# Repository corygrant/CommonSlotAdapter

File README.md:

## CommonSlotAdapter

Adapt HP server power supplies to common high power connectors rather than typical multiple PCI-E connectors.

- Card edge connector: 
    - Amphenol FCI 10053363-200LF [Digikey](https://www.digikey.com/en/products/detail/amphenol-cs-fci/10053363-200LF/1493359?s=N4IgTCBcDaIIwAYEFYDMqBsqC0YkBkAxEAXQF8g)
- Banana jacks: 
    - Cinch 105-0752-001 [Digikey-Red](https://www.digikey.com/en/products/detail/cinch-connectivity-solutions-johnson/105-0752-001/5887) / [Digikey-Black](https://www.digikey.com/en/products/detail/cinch-connectivity-solutions-johnson/105-0753-001/5888) 
- Switch: 
    - Nidec ATE1D-2M3-10-Z [Digikey](https://www.digikey.com/en/products/detail/nidec-components-corporation/ate1d-2m3-10-z/1792018)

Note: I had issues with the typical resistor across 33 and 36. That approach did not work for me. V2 fixes the issues that I had.

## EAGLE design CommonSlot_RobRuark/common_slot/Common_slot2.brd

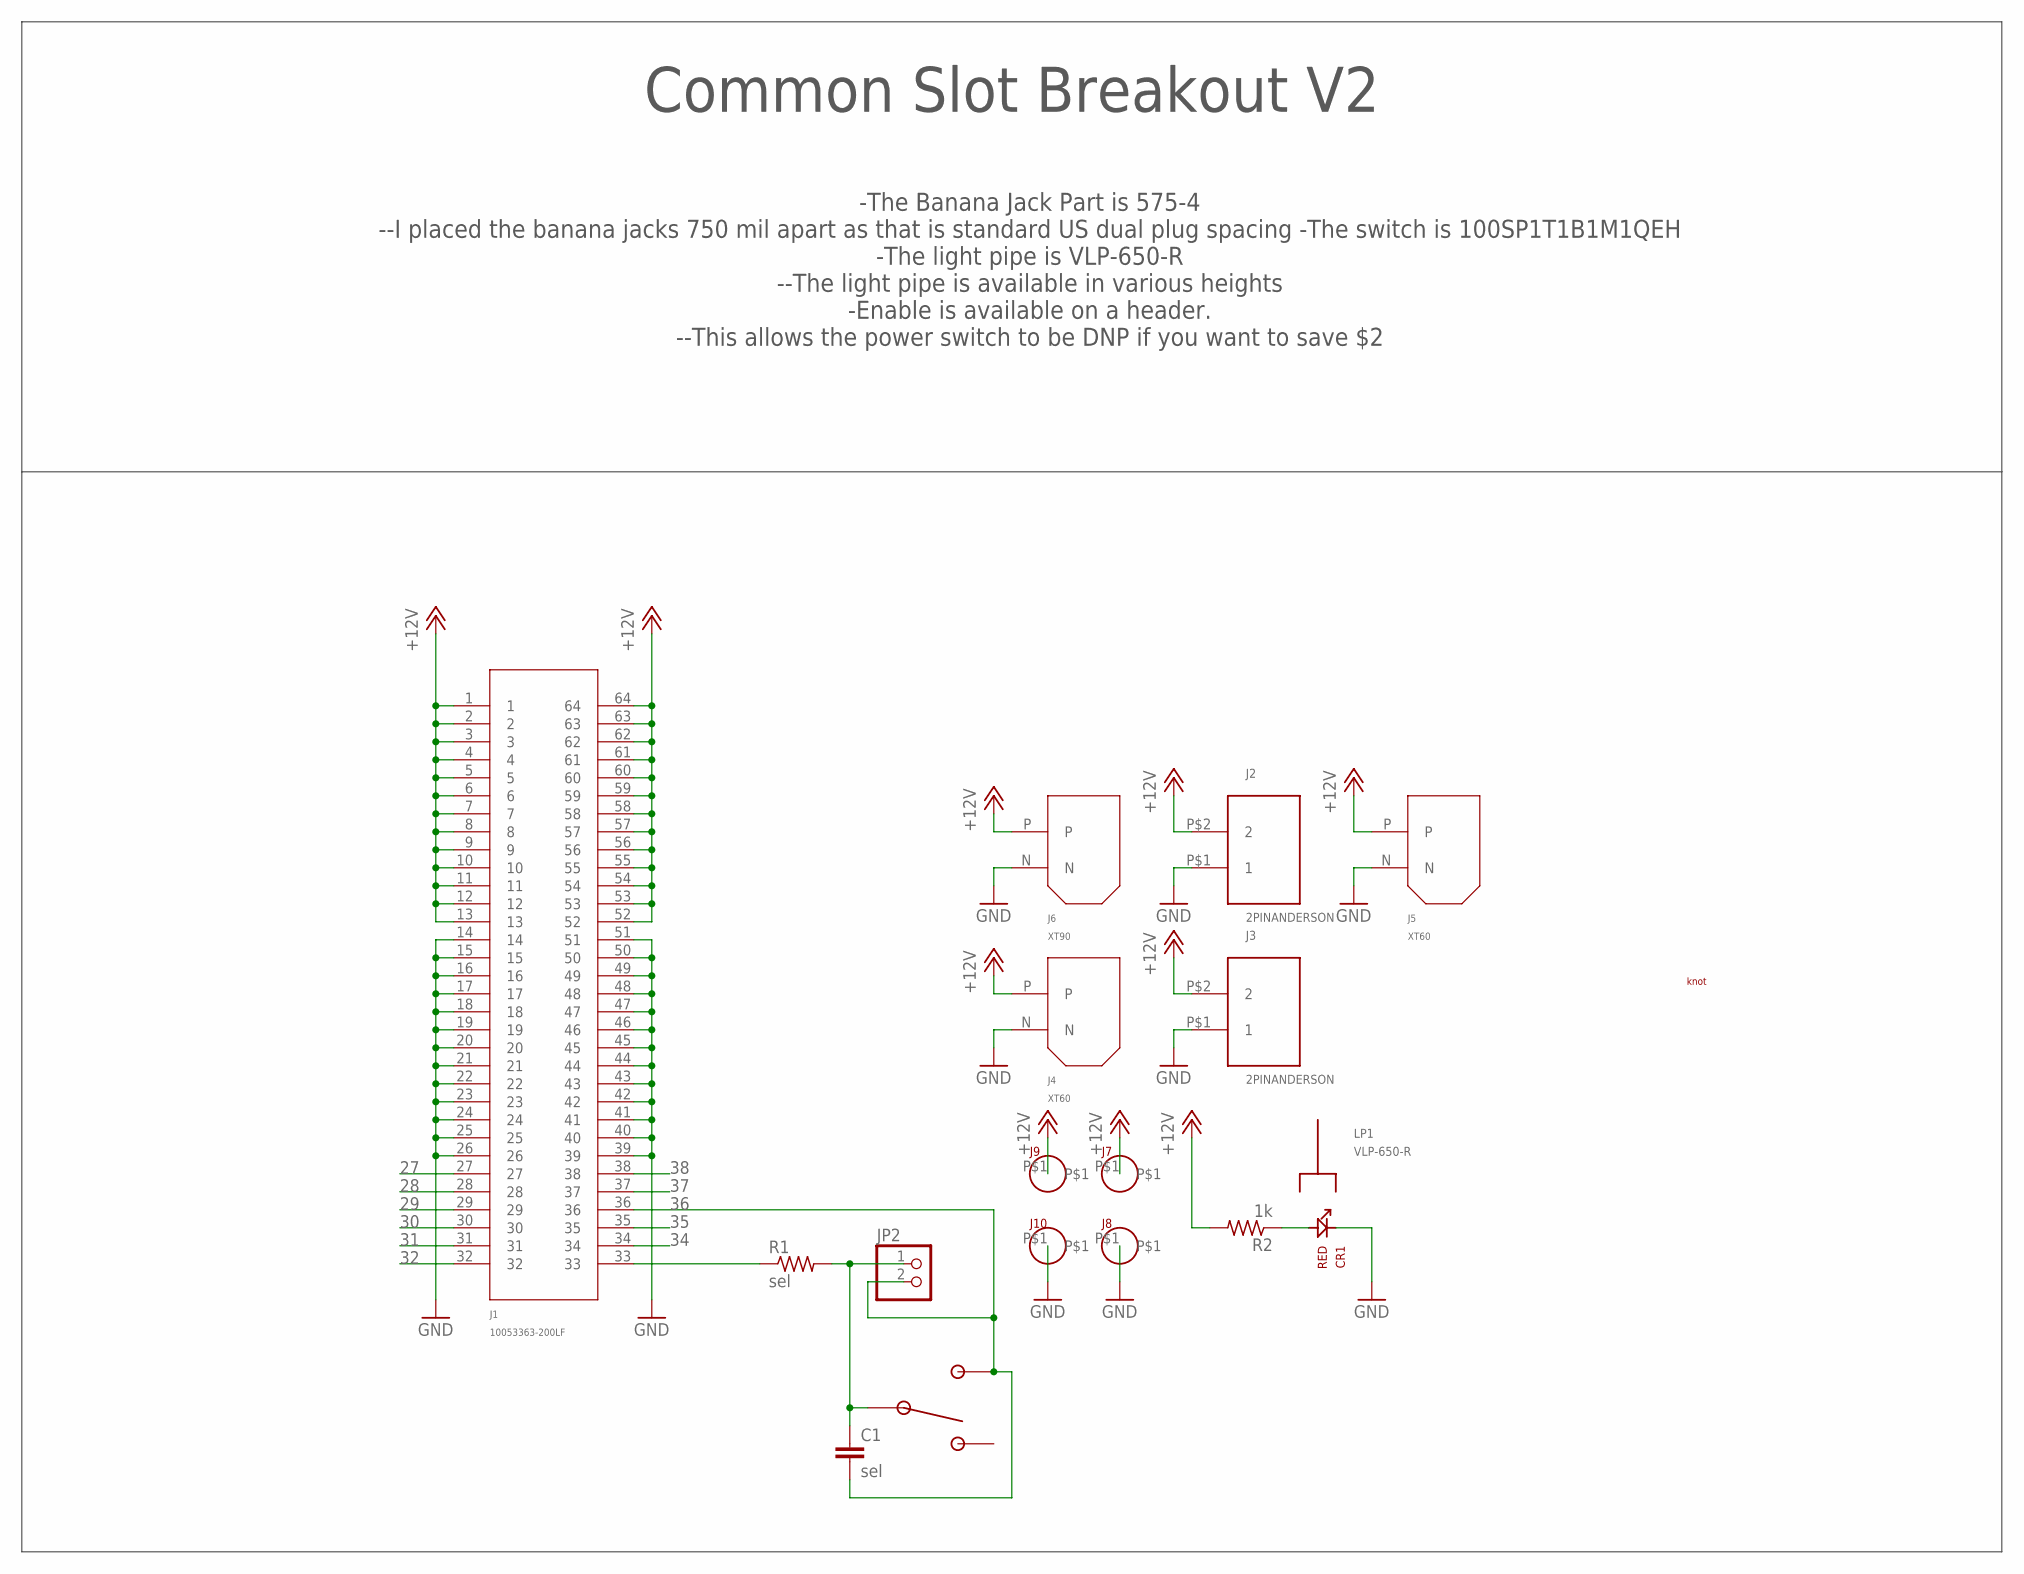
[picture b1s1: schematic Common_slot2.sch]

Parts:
C1: sel; 0603
CR1: RED; 0603_DIODE
J1: 10053363-200LF
J2, J3: 2PINANDERSON; APP
J4, J5: XT60
J6: XT90
J7, J8, J9, J10: BANANA
JP2: PINHD-1X2; 1X02
LP1: VLP-650-R; VLP-XXX-R
R1: sel; 0603
R2: 1k; 0603
SW1: 100SP1T1B1M1QEH
U$1: THIEF_FULL; THIEF_KNOT; PARTNO NA

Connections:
27: J1.27
28: J1.28
29: J1.29
30: J1.30
31: J1.31
32: J1.32
34: J1.34
35: J1.35
36: C1.2, J1.36, JP2.2, SW1.2
37: J1.37
38: J1.38
+12V: J1.1, J1.2, J1.3, J1.4, J1.5, J1.6, J1.7, J1.8, J1.9, J1.10, J1.11, J1.12, J1.13, J1.52, J1.53, J1.54, J1.55, J1.56, J1.57, J1.58, J1.59, J1.60, J1.61, J1.62, J1.63, J1.64, J2.P$2 (2), J3.P$2 (2), J4.P, J5.P, J6.P, J7.P$1, J9.P$1, R2.2
GND: CR1.K, J1.14, J1.15, J1.16, J1.17, J1.18, J1.19, J1.20, J1.21, J1.22, J1.23, J1.24, J1.25, J1.26, J1.39, J1.40, J1.41, J1.42, J1.43, J1.44, J1.45, J1.46, J1.47, J1.48, J1.49, J1.50, J1.51, J2.P$1 (1), J3.P$1 (1), J4.N, J5.N, J6.N, J8.P$1, J10.P$1
unnamed: J1.33, R1.1
unnamed: CR1.A, R2.1
unnamed: C1.1, JP2.1, R1.2, SW1.C (COM)

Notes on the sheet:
Common Slot Breakout V2
-The Banana Jack Part is 575-4 --I placed the banana jacks 750 mil apart as that is standard US dual plug spacing -The switch is 100SP1T1B1M1QEH -The light pipe is VLP-650-R --The light pipe is available in various heights -Enable is available on a header. --This allows the power switch to be DNP i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

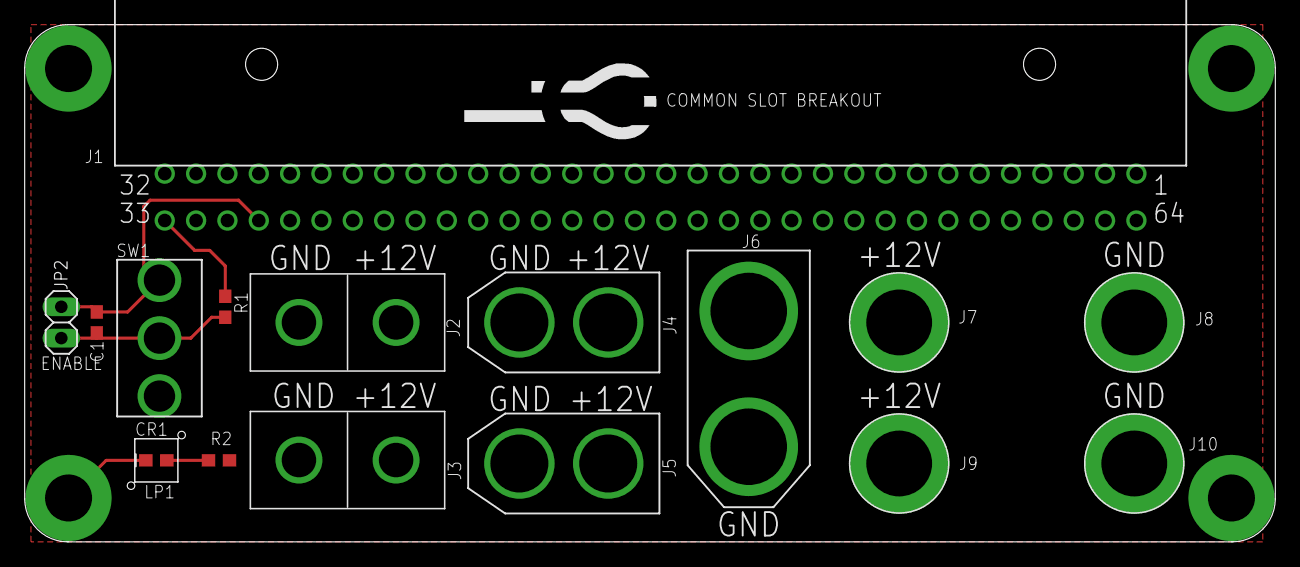
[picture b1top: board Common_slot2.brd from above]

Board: 2 copper layers, 101.3 x 41.9 mm, 18 parts (0 on the bottom side), 6 nets.

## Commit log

2024-09-25 Added Rob Ruark's files
2024-09-25 V1 complete
2024-09-25 Add image
2024-09-25 Add schematic image
2024-09-25 Add step file
2024-10-03 Issue with power output enable
    Version 1 didn't work, version 2 is working
